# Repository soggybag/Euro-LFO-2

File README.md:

# Euro-LFO-2

Claude Conversation about the LFO Math

Here's the whole thing in one place, cleaned up.

## The circuit

```
        R6 10K        SHAPE 500K        D1/D2         RATE 100K
U1B(-) ──/\/\──── wiper ──/\/\──┬──── steering ────── wiper
  │                             │      diodes           │  pin1 = square (U1A out)
 C1 47n (to U1B out)                                     │  pin3 = GND via R4 4K7
                                                    
U1B: integrator   (+in = GND, C1 from out→in, out = triangle)
U1A: Schmitt trig  (-in = GND, +in from R1 150K [own out] and R5 100K [triangle])
     out = square, ±V_sat
```

## Step 1 — Schmitt thresholds set the triangle amplitude

U1A's + input, no current into the pin:

```
V+ = (V_tri·R1 + V_sq·R5) / (R1 + R5)
```

Trips when `V+ = 0`:

```
V_tri,trip = −V_sq · (R5/R1)
```

So the triangle bounces between `±V_sat·(R5/R1)`, giving a peak-to-peak swing:

```
ΔV_pp = 2·V_sat·(R5/R1) = 2·V_sat·(100K/150K) = 1.33·V_sat  ≈ 14 V pp  (±7 V)
```

## Step 2 — Integrator ramp rate

Summing node is a virtual ground, so the timing current is set entirely by the drive voltage and the series resistance:

```
slope = |dV_tri/dt| = V_drive / (R_t · C1)
```

`V_drive` = RATE wiper voltage minus one diode drop; `R_t` = series resistance for that half-cycle.

## Step 3 — Period

Each ramp traverses the **full** pp swing, and the two halves use the two halves of SHAPE (`R_a + R_b = 500K`) with R6 and the RATE source resistance `R_th` in both:

```
T = t_up + t_down
  = 2·(R5/R1)·(V_sat/V_drive)·C1·[ (R6 + R_a + R_th) + (R6 + R_b + R_th) ]
```

```
┌────────────────────────────────────────────────────────────────┐
│  T = 2·(R5/R1)·C1·( 2·R6 + R_SHAPE + 2·R_th ) · V_sat/(V_th−V_f) │
└────────────────────────────────────────────────────────────────┘
```

Key point: **R6 and R_th count twice** (in the path on both ramps); **SHAPE counts once** (the wiper splits it, halves sum to 500 K). That's why SHAPE changes symmetry/PWM but not frequency.

## Idealized form (RATE max, ignore diode)

`V_th → V_sat`, `R_th → 0`, and **V_sat cancels**:

```
        R1                    1
f  ≈  ────── · ──────────────────────────────
        R5       2 · C1 · (2·R6 + R_SHAPE)
```

## Numbers

```
R1/R5 = 1.5
2·C1·(2·R6 + R_SHAPE) = 2·(47 nF)·(20K + 500K) = 0.0489

f_max ≈ 1.5 / 0.0489 ≈ 31 Hz     (T ≈ 33 ms)
```

As RATE turns down, `V_th` falls and stretches the period:

| RATE wiper | V_th | f (approx) |
|---|---|---|
| full up | V_sat | ~30 Hz |
| middle | ~0.5·V_sat | ~14 Hz |
| near bottom | ~0.045·V_sat ≈ 0.47 V | crawls / stalls (below the ~0.5 V diode drop) |

**Practical range ≈ 0.3 Hz to ~30 Hz.**

## Notes

- **V_sat** ≈ ±10.5 V (TL074 stops ~1.5 V short of the rails). It drops out of the ideal formula — bigger swing = taller triangle *and* faster ramp, cancels.
- **Op-amp is now an LM324DT** (JLCPCB basic part C71035, pin-compatible with the TL074). Its swing is asymmetric — about +10.5 V but down to within a few hundred mV of −12 V — so the Schmitt thresholds are uneven: expect a ~0.5 V DC offset on the triangle and SHAPE's 50 % point shifted slightly off centre. Its ~0.4 V/µs slew gives ~50 µs square-wave edges, irrelevant at LFO rates. A TL074 still drops straight in if you want the symmetric JFET behaviour.
- Comparator propagation delay with the LM324 is a few µs vs a 33 ms period → still negligible.
- **V_f** ≈ 0.4–0.5 V steering-diode drop. It does *not* scale with V_sat, so it's what makes the low end nonlinear and adds mild temp drift (−2 mV/°C).
- **To lower the whole range**, scale **C1** up (470 n → ~0.1–3 Hz; 1 µF → ~1.4 Hz max). Don't retune with R5/R1 — that moves amplitude and frequency together.
- **C1 dielectric:** X7R drifts a few % — fine for an LFO. C0G only if you want the rate rock-stable.

Close, but the RATE knob isn't a series resistance you can add — it's a **voltage divider** on the drive (square wave → wiper → GND through R4). So it *multiplies* the rate rather than adding to the timing resistance.

## Ballpark model

**Fast end (RATE maxed)** — the idealized formula as-is:

```
        R1                1                1.5
f_max ≈ ── · ───────────────────────── ≈ ───────────── ≈ 30 Hz
        R5    2·C1·(2·R6 + R_SHAPE)      2·47n·520K
```

**Anywhere else** — scale by the knob:

```
f ≈ f_max · (V_th / V_sat) ≈ f_max · (fraction of knob rotation)
```

roughly linear for a linear-taper pot.

**Slow end (RATE at minimum)** — the drive collapses to the R4 divider:

```
                R4              4.7K
f_min ≈ f_max · ────────── ≈ 30·────── ≈ 1.4 Hz
                R_RATE+R4        104.7K
```

and the ~0.45 V diode drop eats the last sliver, so it actually **stalls at the end stop** — call the usable floor ~1 Hz.

## So

**~1 Hz to ~30 Hz, ~15 Hz at noon.**

## Why "+100K after R_SHAPE" doesn't give the min

The RATE pot's *resistance* contribution (its Thévenin source R looking back into the wiper) only swings from 0 to about **25K** — parallel combination of its two halves — and even at max that changes `f` by ~5%. The 20:1 rate span is entirely the *voltage* division, which is a multiplier, not a term you add to the ohms.

If you want the classic slow-LFO window, scale **C1**: 470 n → ~0.1–3 Hz, 1 µF → ~0.05–1.4 Hz.

It depends on what you want it to modulate, but here are the anchor points:

| Use | Rate | Period |
|---|---|---|
| Slow evolving pad / drone movement | 0.01–0.1 Hz | 10–100 s |
| Once per bar (120 BPM, 4/4) | 0.5 Hz | 2 s |
| Once per beat (120 BPM) | 2 Hz | 0.5 s |
| Rhythmic "wobble" | 1–8 Hz | — |
| Vibrato / tremolo | 4–8 Hz | — |
| Buzzy / edge-of-audio modulation | 20–30 Hz | — |
| Audio-rate (through-zero FM, AM, LFO-as-oscillator) | 30 Hz–2 kHz | — |

## The all-rounder target

A standalone modulation LFO wants roughly **0.05 Hz (≈20 s) to ~20 Hz** — that covers "slow filter sweep" up through "vibrato." The catch is that's a ~400:1 span, and a single knob over that range feels terrible with a linear taper (everything useful is crammed into the last few degrees). So real LFOs do one of:

- **Tapered pot** — reverse-log / "C" taper on RATE so the slow-to-medium zone gets most of the rotation.
- **Range switch** — a 2- or 3-position switch that swaps the timing cap, e.g. slow / med / fast.
- Both.

Extending the top past ~30 Hz into audio rate is a nice bonus but a separate design goal — this TL074 + diode-shaper topology isn't built for clean audio-rate output, so I'd not chase it here.

## For your circuit

Your span ratio is locked at about `(R_RATE + R4)/R4 ≈ 22:1` by the RATE divider. C1 just slides that 22:1 window up or down:

| C1 | Range | Character |
|---|---|---|
| 47 nF (now) | ~1.4–30 Hz | fast LFO — no slow sweeps |
| **100 nF** | **~0.7–14 Hz** | good general-purpose single range |
| 220 nF | ~0.3–6 Hz | slow/medium |
| 1 µF | ~0.06–1.4 Hz | slow-only |

My suggestion: **C1 = 100 nF** for a better single-range LFO, plus a **SPDT range switch** paralleling a larger cap (say +2.2 µF) to drop into a slow mode (~0.03–0.6 Hz) when you want it. And swap RATE to a reverse-log pot.

Don't try to widen the 22:1 span much by shrinking R4 — the steering diodes need the wiper voltage to stay above ~1 V to keep oscillating, so the bottom of the knob just goes mushy and stalls rather than getting genuinely slow. Sliding the window with C1 (or switching it) is the reliable lever.

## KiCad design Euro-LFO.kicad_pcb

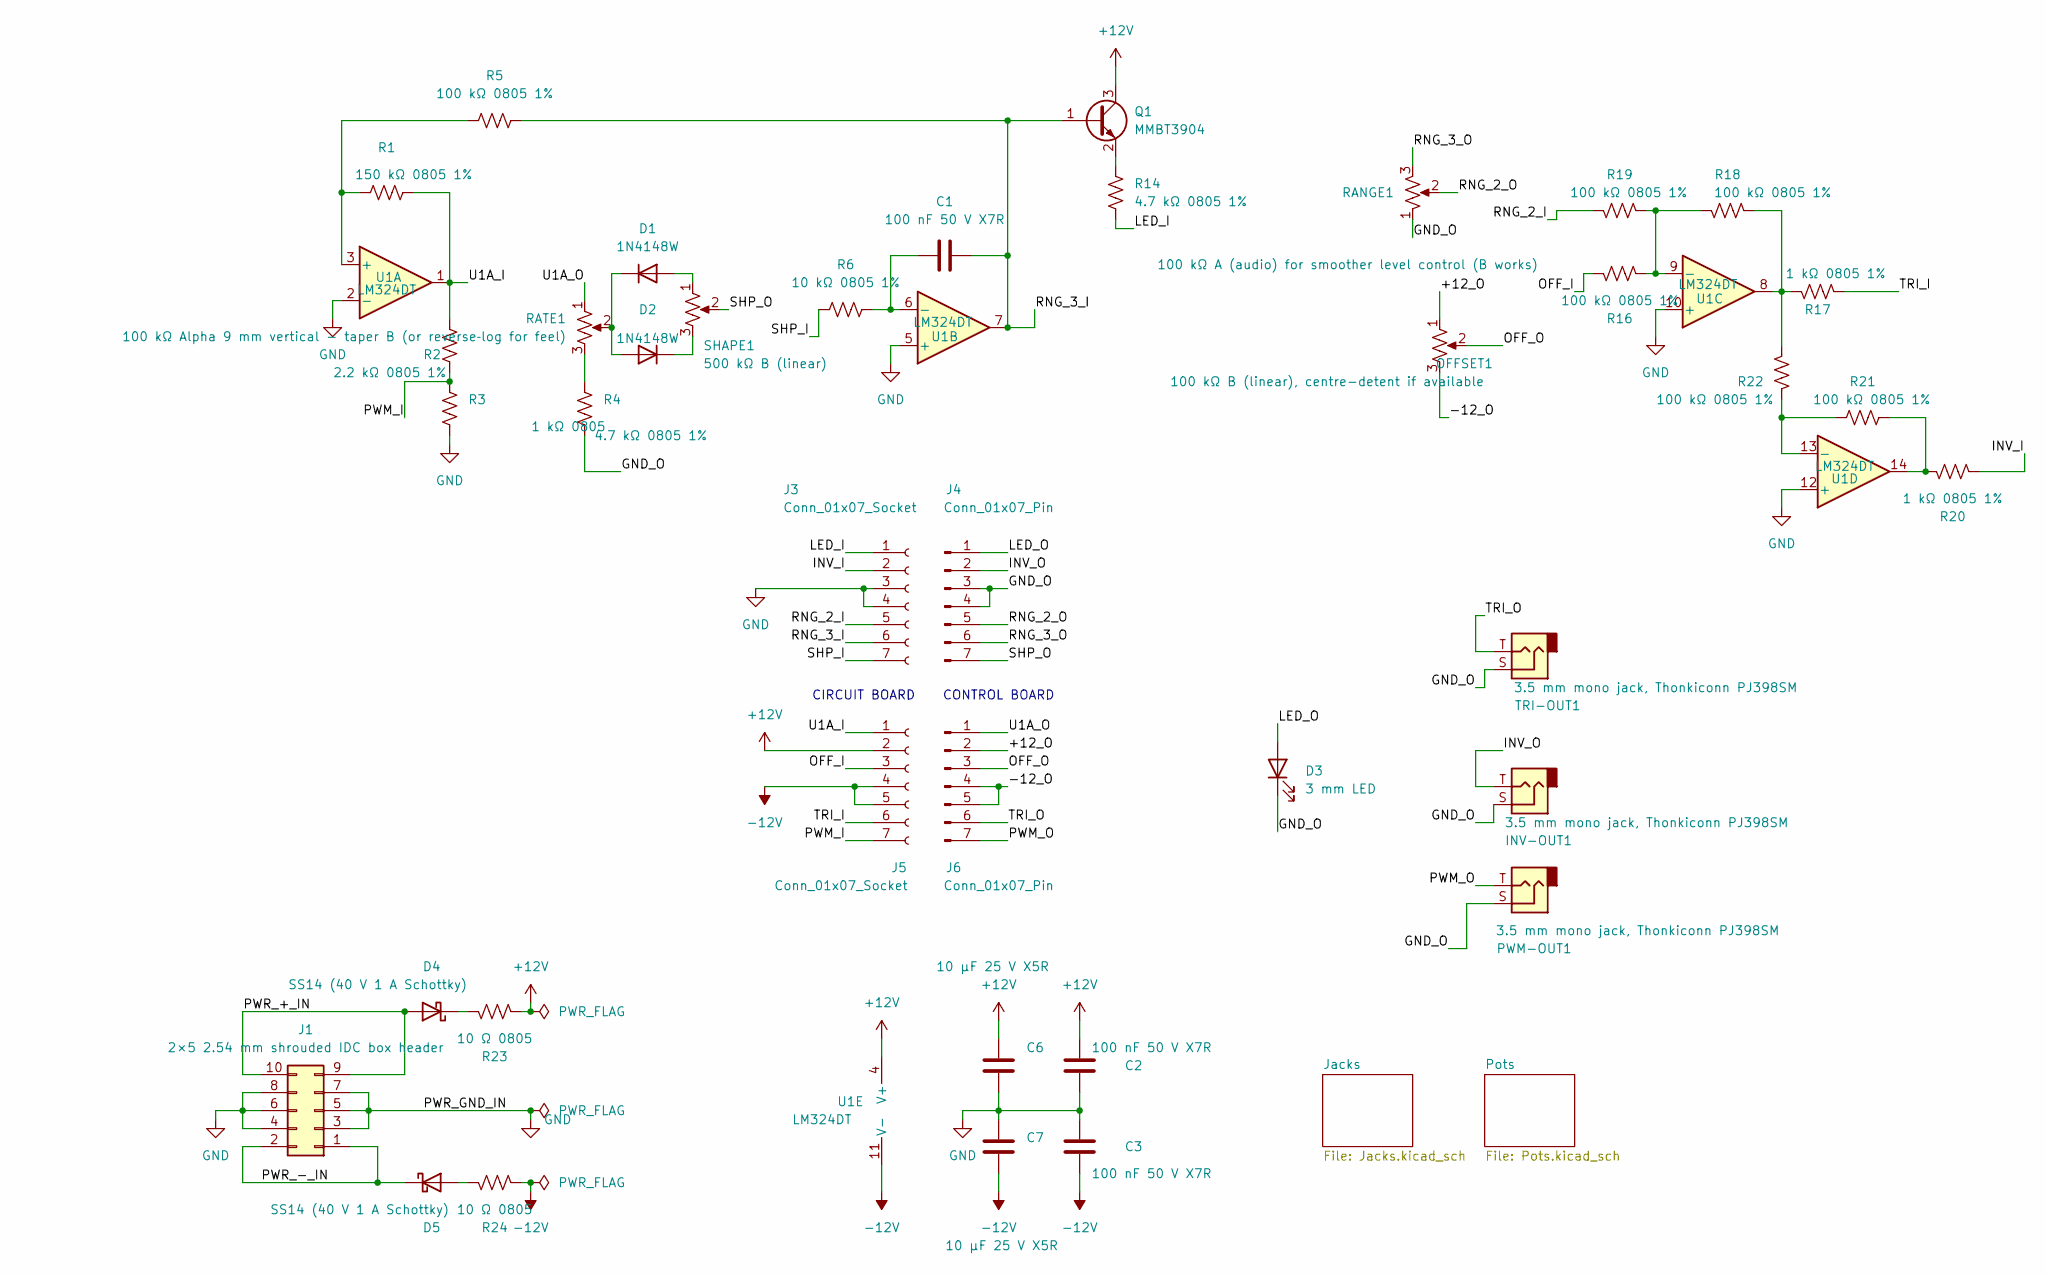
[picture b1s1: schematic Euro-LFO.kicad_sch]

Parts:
C1, C2, C3: 100 nF 50 V X7R; C_0805_2012Metric; LCSC C49678
C6, C7: 10 µF 25 V X5R; C_0805_2012Metric; LCSC C15850
D1, D2: 1N4148W; D_SOD-123; LCSC C81598
D3: 3 mm LED; LED_D3.0mm
D4, D5: SS14 (40 V 1 A Schottky); D_SMA; LCSC C2480
INV-OUT1: 3.5 mm mono jack, Thonkiconn PJ398SM; Jack_3.5mm_QingPu_WQP-PJ398SM_Vertical_CircularHoles
J1: 2×5 2.54 mm shrouded IDC box header; IDC-Header_2x05_P2.54mm_Vertical
J3, J5: Conn_01x07_Socket; PinSocket_1x07_P2.54mm_Vertical
J4, J6: Conn_01x07_Pin; PinHeader_1x07_P2.54mm_Vertical
OFFSET1: 100 kΩ B (linear), centre-detent if available; Potentiometer_Alpha_RD901F-40-00D_Single_Vertical
PWM-OUT1: 3.5 mm mono jack, Thonkiconn PJ398SM; Jack_3.5mm_QingPu_WQP-PJ398SM_Vertical_CircularHoles
Q1: MMBT3904; SOT-23; LCSC C20526
R1: 150 kΩ 0805 1%; R_0805_2012Metric; LCSC C17470
R2: 2.2 kΩ 0805 1%; R_0805_2012Metric; LCSC C17520
R3: 1 kΩ 0805; R_0805_2012Metric; LCSC C17513
R4, R14: 4.7 kΩ 0805 1%; R_0805_2012Metric; LCSC C17673
R5, R16, R18, R19, R21, R22: 100 kΩ 0805 1%; R_0805_2012Metric; LCSC C149504
R6: 10 kΩ 0805 1%; R_0805_2012Metric; LCSC C17414
R17, R20: 1 kΩ 0805 1%; R_0805_2012Metric; LCSC C17513
R23, R24: 10 Ω 0805; R_0805_2012Metric; LCSC C17415
RANGE1: 100 kΩ A (audio) for smoother level control (B wo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; Potentiometer_Alpha_RD901F-40-00D_Single_Vertical
RATE1: 100 kΩ Alpha 9 mm vertical - taper B (or reverse‑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; Potentiometer_Alpha_RD901F-40-00D_Single_Vertical
SHAPE1: 500 kΩ B (linear); Potentiometer_Alpha_RD901F-40-00D_Single_Vertical
TRI-OUT1: 3.5 mm mono jack, Thonkiconn PJ398SM; Jack_3.5mm_QingPu_WQP-PJ398SM_Vertical_CircularHoles
U1: LM324DT; SO-14_3.9x8.65mm_P1.27mm; LCSC C71035

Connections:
+12V: C2.1, C6.1, J5.2, Q1.3 (C), R23.1, U1.4 (V+)
-12V: C3.2, C7.2, J5.4, J5.5, R24.1, U1.11 (V-)
/+12_O: J6.2, OFFSET1.1
/-12_O: J6.4, J6.5, OFFSET1.3
/GND_O: D3.1 (K), INV-OUT1.S, J4.3, J4.4, PWM-OUT1.S, R4.1, RANGE1.1, TRI-OUT1.S
/INV_I: J3.2, R20.1
/INV_O: INV-OUT1.T, J4.2
/LED_I: J3.1, R14.2
/LED_O: D3.2 (A), J4.1
/OFF_I: J5.3, R16.2
/OFF_O: J6.3, OFFSET1.2
/PWM_I: J5.7, R2.1, R3.2
/PWM_O: J6.7, PWM-OUT1.T
/PWR_+_IN: D4.2 (A), J1.9, J1.10
/PWR_-_IN: D5.1 (K), J1.1, J1.2
/RNG_2_I: J3.5, R19.2
/RNG_2_O: J4.5, RANGE1.2
/RNG_3_I: C1.2, J3.6, Q1.1 (B), R5.1, U1.7
/RNG_3_O: J4.6, RANGE1.3
/SHP_I: J3.7, R6.2
/SHP_O: J4.7, SHAPE1.2
/TRI_I: J5.6, R17.1
/TRI_O: J6.6, TRI-OUT1.T
/U1A_I: J5.1, R1.2, R2.2, U1.1
/U1A_O: J6.1, RATE1.1
GND: C2.2, C3.1, C6.2, C7.1, J1.3, J1.4, J1.5, J1.6, J1.7, J1.8, J3.3, J3.4, R3.1, U1.2 (-), U1.5 (+), U1.10 (+), U1.12 (+)
unnamed: D1.2 (A), SHAPE1.1
unnamed: D1.1 (K), D2.2 (A), RATE1.2
unnamed: D2.1 (K), SHAPE1.3
unnamed: D4.1 (K), R23.2
unnamed: D5.2 (A), R24.2
unnamed: Q1.2 (E), R14.1
unnamed: R4.2, RATE1.3
unnamed: R17.2, R18.1, R22.1, U1.8
unnamed: R20.2, R21.1, U1.14
unnamed: R1.1, R5.2, U1.3 (+)
unnamed: C1.1, R6.1, U1.6 (-)
unnamed: R16.1, R18.2, R19.1, U1.9 (-)
unnamed: R21.2, R22.2, U1.13 (-)

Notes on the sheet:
CONTROL BOARD
CIRCUIT BOARD

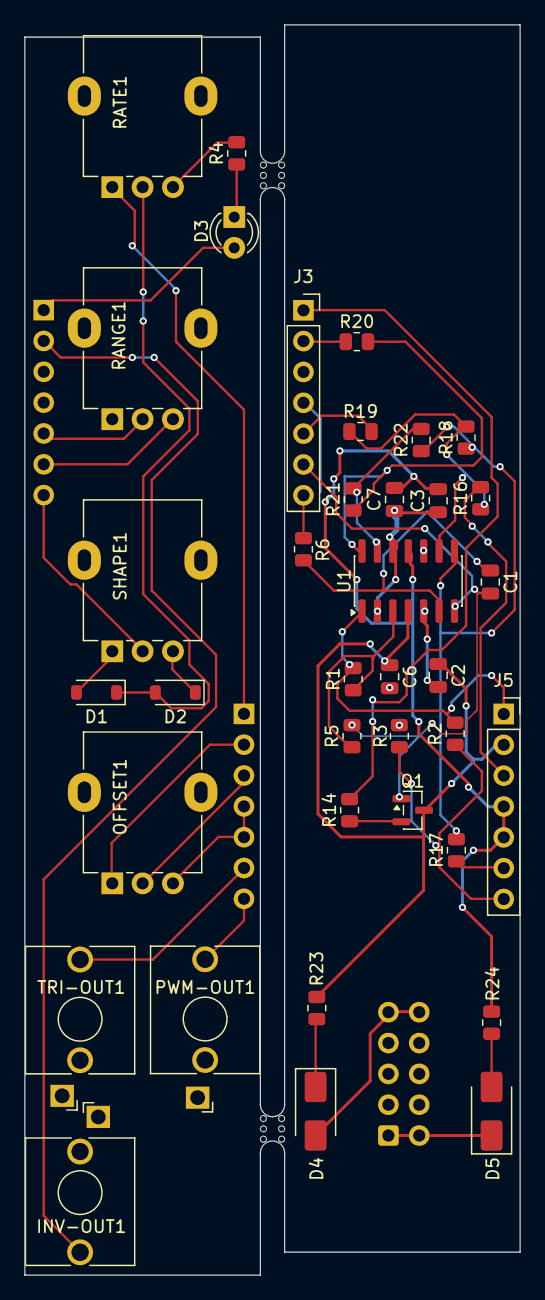
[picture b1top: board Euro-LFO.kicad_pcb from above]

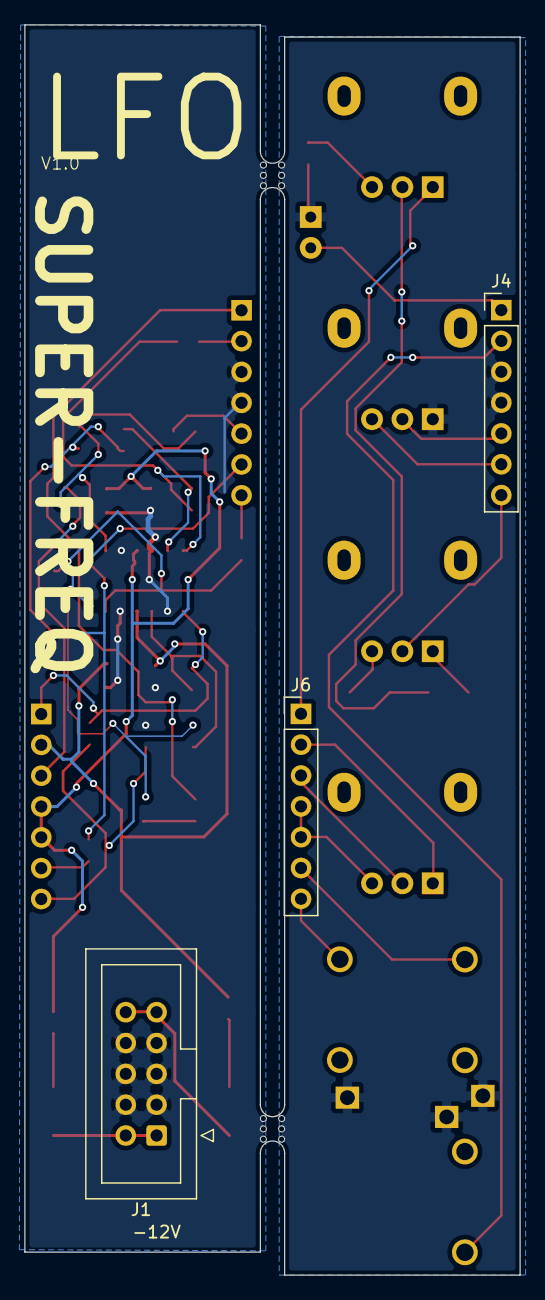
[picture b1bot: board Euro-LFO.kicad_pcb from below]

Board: 2 copper layers, 40.8 x 103.0 mm, 40 parts (3 on the bottom side), 39 nets.
